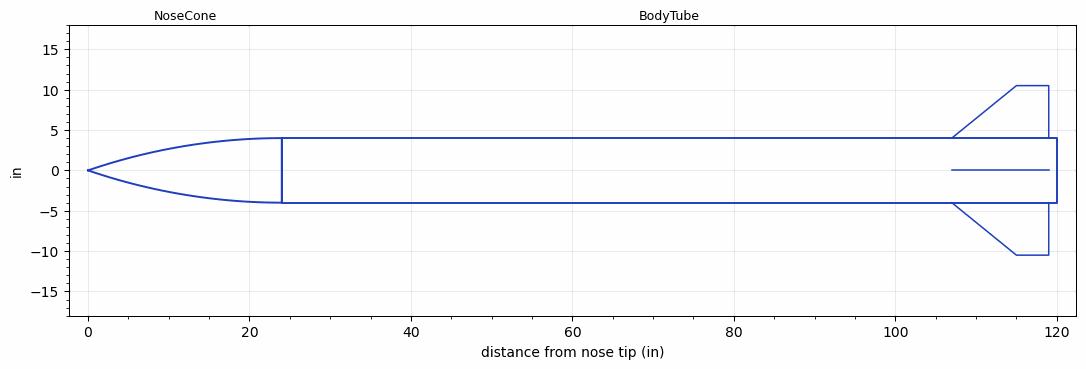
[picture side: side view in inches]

<RASAeroDocument>
 <FileVersion>2</FileVersion>
 <RocketDesign>
  <NoseCone>
   <Length>24.0</Length>
   <Diameter>8.0</Diameter>
   <Shape>Tangent Ogive</Shape>
   <Location>0.0</Location>
  </NoseCone>
  <BodyTube>
   <Length>95.9998</Length>
   <Diameter>8.0</Diameter>
   <Location>24.0</Location>
   <Fin>
    <Count>4</Count>
    <Chord>12.0</Chord>
    <Span>6.5</Span>
    <SweepDistance>8.0</SweepDistance>
    <TipChord>4.0</TipChord>
    <Thickness>0.25</Thickness>
    <Location>13.0</Location>
    <AirfoilSection>Hexagonal Blunt Base</AirfoilSection>
    <FX1>0.5</FX1>
   </Fin>
  </BodyTube>
  <Surface>Smooth (Zero Roughness)</Surface>
  <ModifiedBarrowman>False</ModifiedBarrowman>
  <Turbulence>True</Turbulence>
  <UseBooster1>False</UseBooster1>
  <UseBooster2>False</UseBooster2>
  <Comments>Extended controlled aerodynamic study: Hbev-scale2</Comments>
 </RocketDesign>
 <LaunchSite>
  <Altitude>0</Altitude>
  <Pressure>29.9214</Pressure>
  <RodAngle>0</RodAngle>
  <RodLength>6.5617</RodLength>
  <Temperature>59</Temperature>
  <WindSpeed>0</WindSpeed>
 </LaunchSite>
 <Recovery>
  <Altitude1>656.168</Altitude1>
  <Altitude2>0</Altitude2>
  <DeviceType1>Parachute</DeviceType1>
  <DeviceType2>None</DeviceType2>
  <Event1>True</Event1>
  <Event2>False</Event2>
  <Size1>24</Size1>
  <Size2>0</Size2>
  <EventType1>Apogee</EventType1>
  <EventType2>None</EventType2>
  <CD1>0.8</CD1>
  <CD2>0</CD2>
 </Recovery>
 <SimulationList>
  <Simulation>
   <SustainerEngine>I500T-14A  (AT)</SustainerEngine>
   <SustainerLaunchWt>14.5064</SustainerLaunchWt>
   <SustainerCG>34.7639</SustainerCG>
   <SustainerIgnitionDelay>0</SustainerIgnitionDelay>
   <Booster1SeparationDelay>0</Booster1SeparationDelay>
   <Booster1IgnitionDelay>0</Booster1IgnitionDelay>
   <IncludeBooster1>False</IncludeBooster1>
   <Booster2Delay>0</Booster2Delay>
   <IncludeBooster2>False</IncludeBooster2>
   <TimetoApogee>9.190115</TimetoApogee>
   <MaxAltitude>1235.54</MaxAltitude>
   <MaxVelocity>270.5551</MaxVelocity>
  </Simulation>
  <Simulation>
   <SustainerEngine>J570W  (AT)</SustainerEngine>
   <SustainerLaunchWt>15.1813</SustainerLaunchWt>
   <SustainerCG>35.261</SustainerCG>
   <SustainerIgnitionDelay>0</SustainerIgnitionDelay>
   <Booster1SeparationDelay>0</Booster1SeparationDelay>
   <Booster1IgnitionDelay>0</Booster1IgnitionDelay>
   <IncludeBooster1>False</IncludeBooster1>
   <Booster2Delay>0</Booster2Delay>
   <IncludeBooster2>False</IncludeBooster2>
   <TimetoApogee>13.66022</TimetoApogee>
   <MaxAltitude>2940.604</MaxAltitude>
   <MaxVelocity>432.8058</MaxVelocity>
  </Simulation>
 </SimulationList>
</RASAeroDocument>
